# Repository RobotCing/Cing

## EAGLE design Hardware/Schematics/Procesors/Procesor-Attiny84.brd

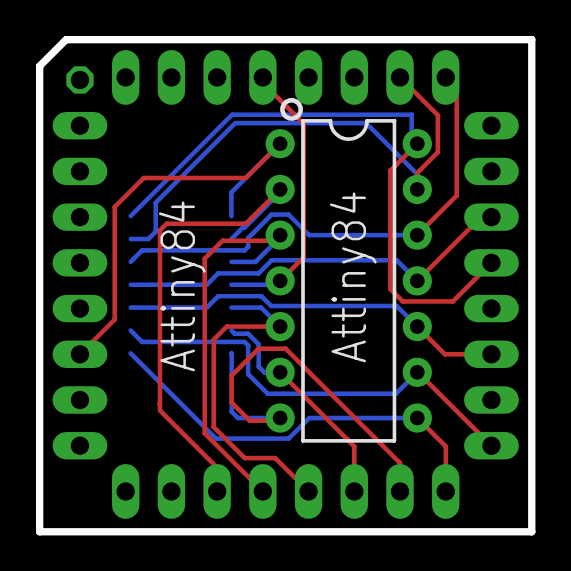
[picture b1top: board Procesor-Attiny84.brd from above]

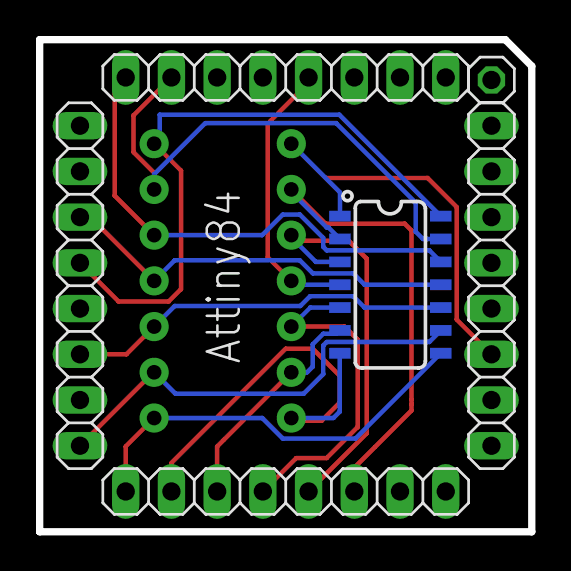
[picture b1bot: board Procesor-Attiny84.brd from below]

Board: 2 copper layers, 27.3 x 27.3 mm, 7 parts (6 on the bottom side), 14 nets.

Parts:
E$1: DIP14
E$2: 1X01
E$3: SO14
E$9, E$10, E$11, E$12: 1X08

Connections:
S$2: E$1.4, E$3.4, E$10.5
S$3: E$1.14, E$3.14, E$11.4
S$4: E$1.1, E$3.1, E$9.3
S$5: E$1.9, E$3.9, E$11.8
S$6: E$1.12, E$3.12, E$10.1
S$7: E$1.13, E$3.13, E$10.2
S$8: E$1.7, E$3.7, E$12.7
S$10: E$1.8, E$3.8, E$12.8
S$11: E$1.10, E$3.10, E$11.6
S$12: E$1.11, E$3.11, E$11.3
S$13: E$1.2, E$3.2, E$12.3
S$14: E$1.3, E$3.3, E$12.4
S$15: E$1.5, E$3.5, E$12.5
S$18: E$1.6, E$3.6, E$12.6

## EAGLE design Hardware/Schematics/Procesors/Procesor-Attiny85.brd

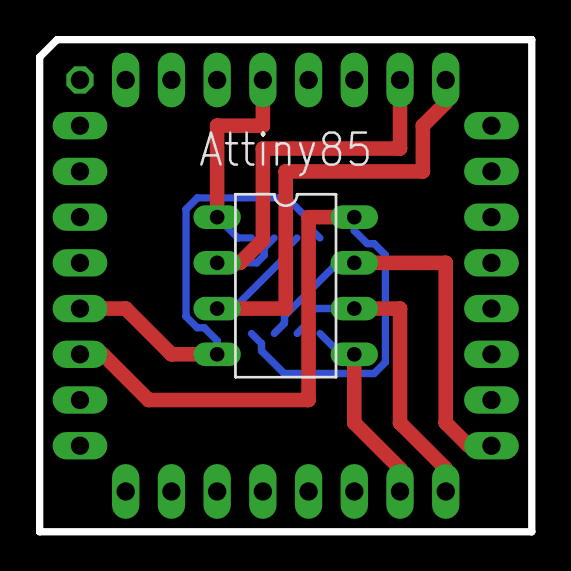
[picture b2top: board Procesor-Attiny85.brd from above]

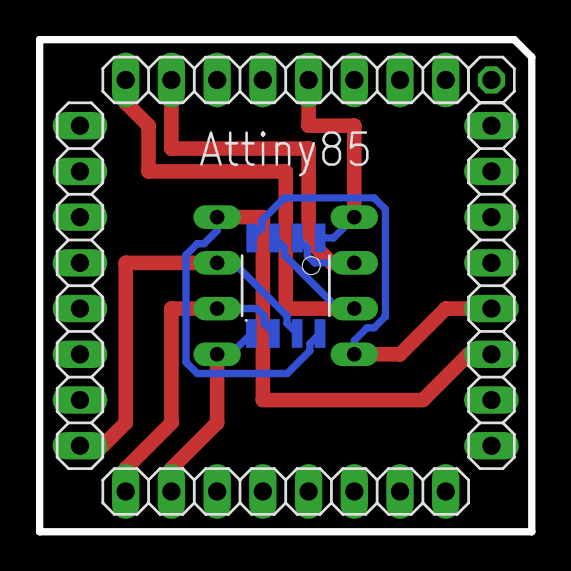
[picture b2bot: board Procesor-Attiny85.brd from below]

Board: 2 copper layers, 27.3 x 27.3 mm, 7 parts (6 on the bottom side), 8 nets.

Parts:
ATTINY85: DIL08
E$1: 1X01
E$2: 8S1
E$9, E$10, E$11, E$12: 1X08

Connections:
S$2: ATTINY85.1, E$2.1, E$10.5
S$3: ATTINY85.4, E$2.4, E$9.4
S$4: ATTINY85.8, E$2.8, E$9.3
S$5: ATTINY85.7, E$2.7, E$11.8
S$6: ATTINY85.3, E$2.3, E$10.1
S$7: ATTINY85.2, E$2.2, E$10.2
S$8: ATTINY85.5, E$2.5, E$12.7
S$10: ATTINY85.6, E$2.6, E$12.8

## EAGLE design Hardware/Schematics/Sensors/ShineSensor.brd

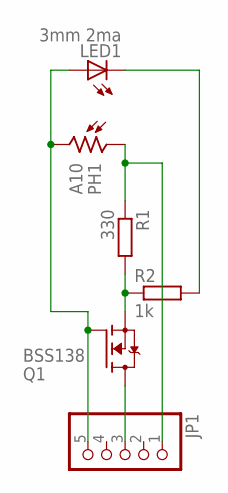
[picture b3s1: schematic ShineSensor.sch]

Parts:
JP1: PINHD-1X5; 1X05
LED1: 3mm 2ma; LED3MM
PH1: A10; T0-46-A10XX
Q1: BSS138; SOT23
R1: 330; R1206
R2: 1k; R1206

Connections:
unnamed: JP1.5, LED1.A, PH1.2, Q1.1 (G)
unnamed: LED1.K (C), R2.2
unnamed: JP1.3, Q1.3 (D)
unnamed: JP1.1, PH1.1, R1.1
unnamed: Q1.2 (S), R1.2, R2.1

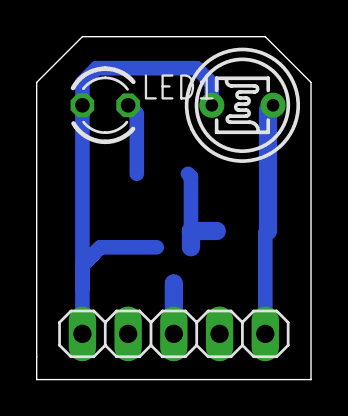
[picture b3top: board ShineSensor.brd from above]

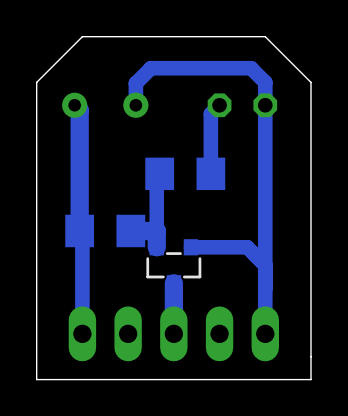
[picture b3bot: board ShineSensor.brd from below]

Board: 2 copper layers, 15.2 x 19.1 mm, 6 parts (3 on the bottom side), 5 nets.

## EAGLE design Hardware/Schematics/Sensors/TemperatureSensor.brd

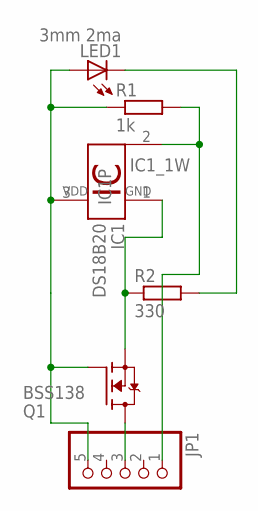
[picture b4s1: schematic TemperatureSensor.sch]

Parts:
IC1: DS18B20; TO92-
JP1: PINHD-1X5; 1X05
LED1: 3mm 2ma; LED3MM
Q1: BSS138; SOT23
R1: 1k; R1206
R2: 330; R1206

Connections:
unnamed: IC1.3 (VDD), JP1.5, LED1.A, Q1.1 (G), R1.1
unnamed: LED1.K (C), R2.2
unnamed: JP1.3, Q1.3 (D)
unnamed: IC1.1 (GND), Q1.2 (S), R2.1
unnamed: IC1.2 (1W), JP1.1, R1.2

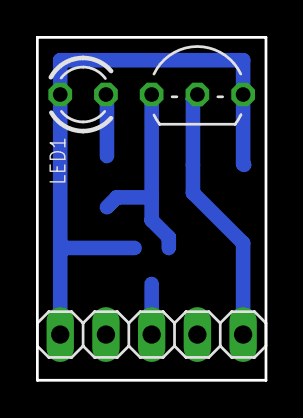
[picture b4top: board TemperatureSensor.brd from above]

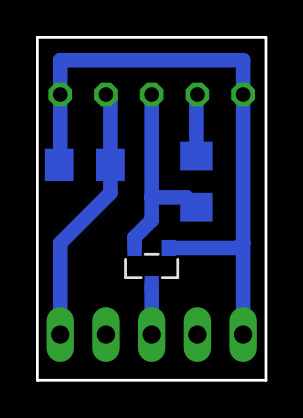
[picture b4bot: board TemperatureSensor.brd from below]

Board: 2 copper layers, 12.7 x 19.1 mm, 6 parts (3 on the bottom side), 5 nets.

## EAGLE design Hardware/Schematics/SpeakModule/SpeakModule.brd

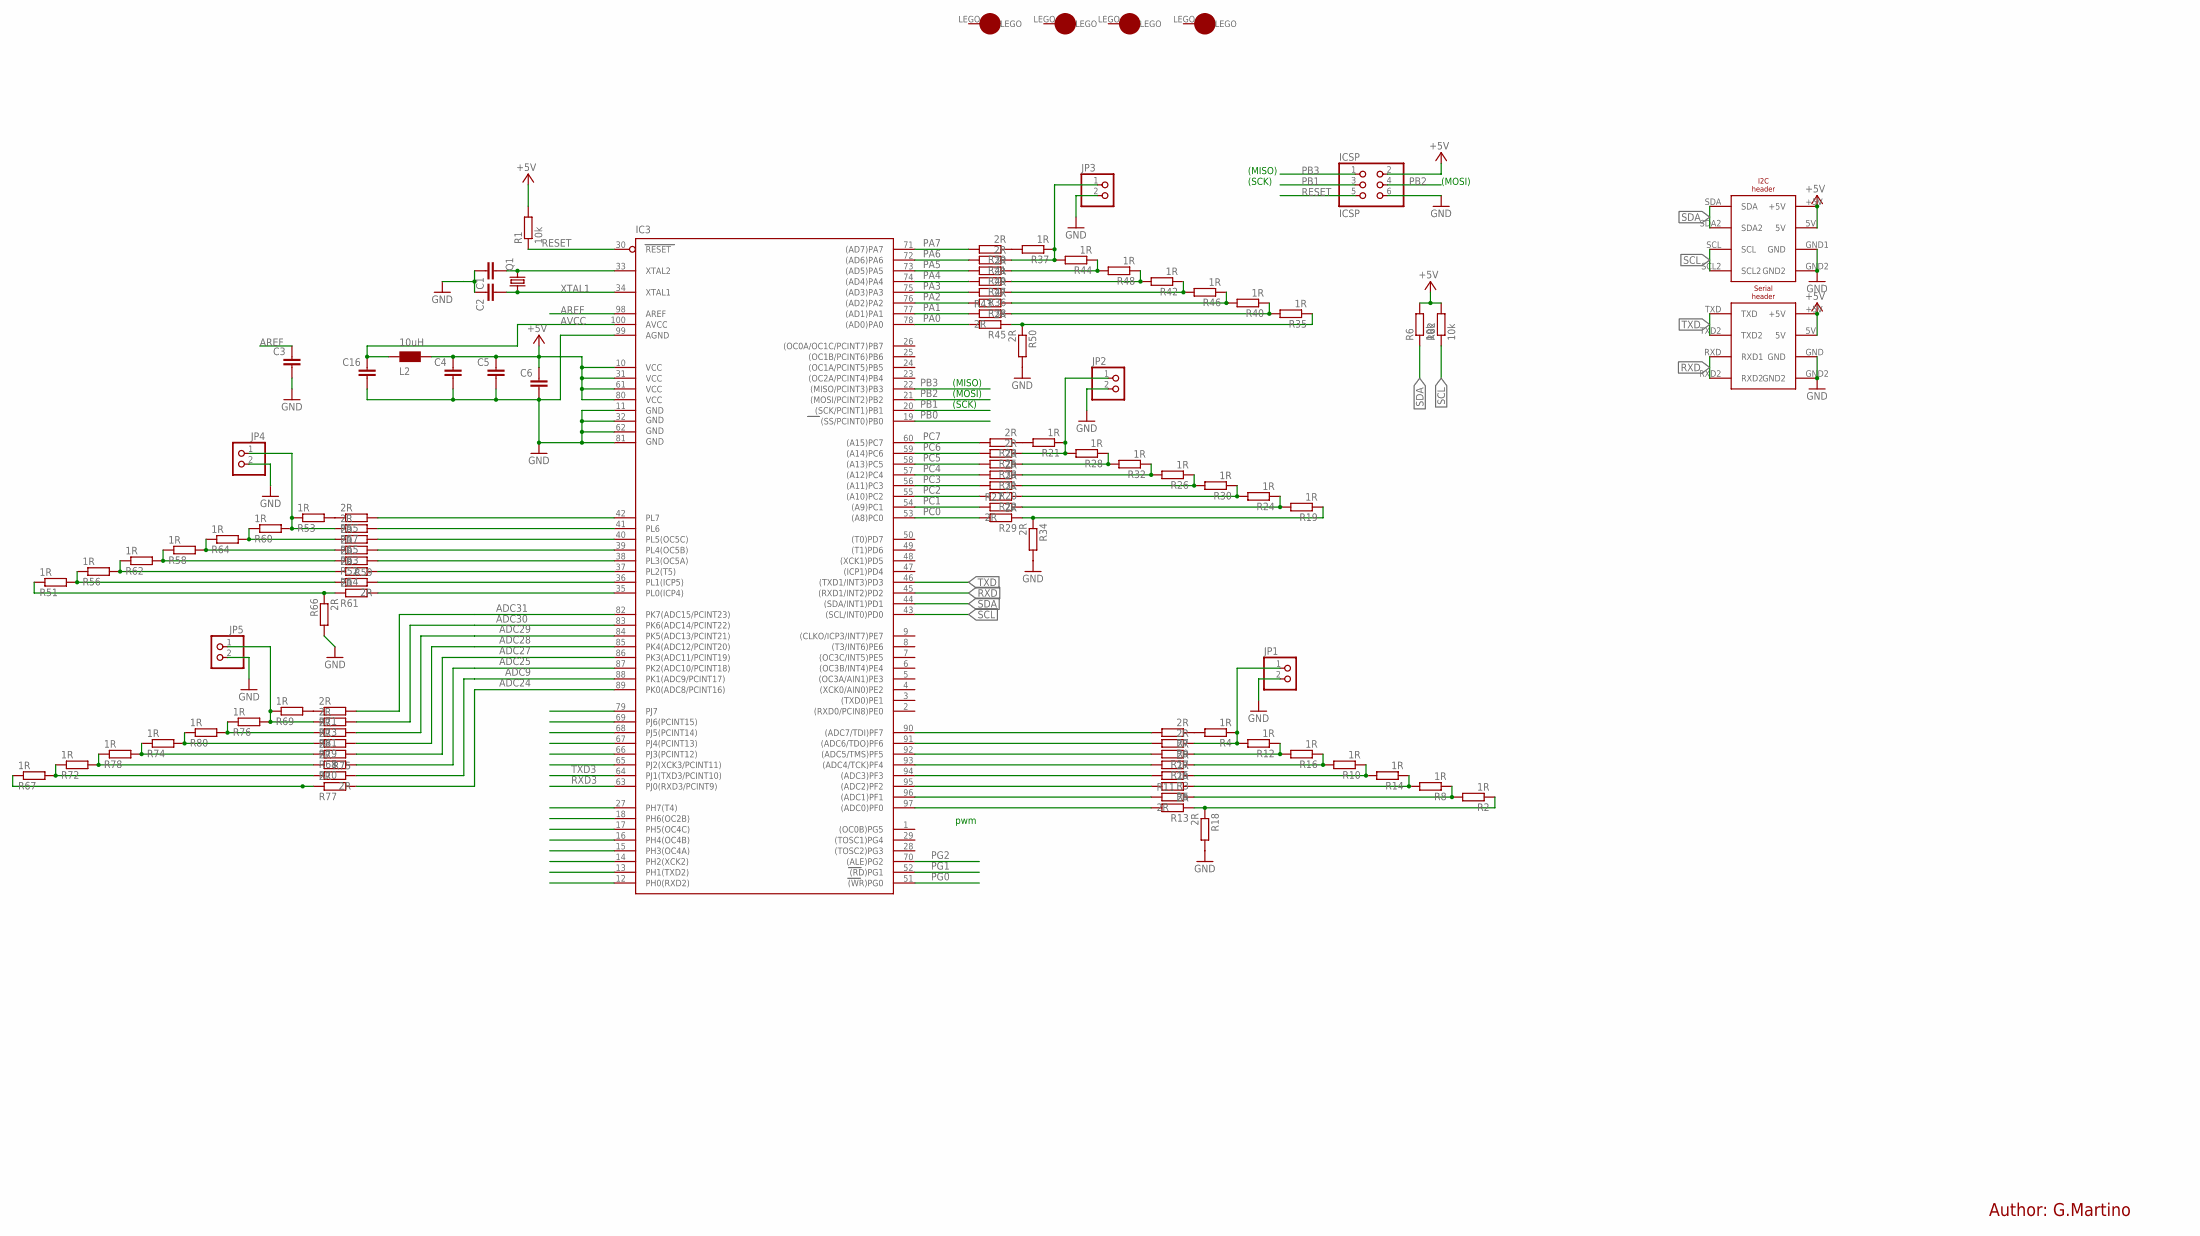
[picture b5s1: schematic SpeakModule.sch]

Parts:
C1, C2: 22pf; C1206
C3, C4, C5, C6, C16: 100nF; C1206
IC3: ATMEGA2560-15AU; TQFP100
ICSP: ICSP; 2X03
JP1, JP2, JP3, JP4, JP5: PINHD-1X2; 1X02
L2: 10uH; 0805
Q1: CRYSTALHC49S; HC49/S
R1, R6, R82: 10k; M1206
R2, R4, R8, R10, R12, R14, R16, R19, R21, R24, R26, R28, R30, R32, R35, R37, R40, R42, R44, R46, R48, R51, R53, R56, R58, R60, R62, R64, R67, R69, R72, R74, R76, R78, R80: 1R; M1206
R3, R5, R7, R9, R11, R13, R15, R17, R18, R20, R22, R23, R25, R27, R29, R31, R33, R34, R36, R38, R39, R41, R43, R45, R47, R49, R50, R52, R54, R55, R57, R59, R61, R63, R65, R66, R68, R70, R71, R73, R75, R77, R79, R81: 2R; M1206
U$1, U$2, U$3, U$4: LEGO-1X1
U$5: I2C_HEADER; I2_HEADER
U$6: SERIAL_HEADER

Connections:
+5V: C4.1, C5.1, C6.1, IC3.10 (VCC), IC3.31 (VCC1), IC3.61 (VCC2), IC3.80 (VCC3), ICSP.2, L2.2, R1.2, R6.2, R82.2, U$5.5V, U$5.+5V, U$6.5V, U$6.+5V
ADC0: IC3.97 ((ADC0)PF0), R13.2
ADC1: IC3.96 ((ADC1)PF1), R11.1
ADC2: IC3.95 ((ADC2)PF2), R5.2
ADC3: IC3.94 ((ADC3)PF3), R3.2
ADC4: IC3.93 ((ADC4/TCK)PF4), R15.2
ADC5: IC3.92 ((ADC5/TMS)PF5), R17.2
ADC6: IC3.91 ((ADC6/TDO)PF6), R9.2
ADC7: IC3.90 ((ADC7/TDI)PF7), R7.2
ADC9: IC3.88 (PK1(ADC9/PCINT17)), R75.1
ADC16: IC3.35 (PL0(ICP4)), R61.2
ADC17: IC3.37 (PL2(T5)), R54.2
ADC18: IC3.36 (PL1(ICP5)), R59.1
ADC19: IC3.38 (PL3(OC5A)), R52.2
ADC20: IC3.39 (PL4(OC5B)), R63.2
ADC21: IC3.40 (PL5(OC5C)), R65.2
ADC22: IC3.41 (PL6), R57.2
ADC23: IC3.42 (PL7), R55.2
ADC24: IC3.89 (PK0(ADC8/PCINT16)), R77.2
ADC25: IC3.87 (PK2(ADC10/PCINT18)), R70.2
ADC27: IC3.86 (PK3(ADC11/PCINT19)), R68.2
ADC28: IC3.85 (PK4(ADC12/PCINT20)), R79.2
ADC29: IC3.84 (PK5(ADC13/PCINT21)), R81.2
ADC30: IC3.83 (PK6(ADC14/PCINT22)), R73.2
ADC31: IC3.82 (PK7(ADC15/PCINT23)), R71.2
AREF: C3.1, IC3.98 (AREF)
AVCC: C16.1, IC3.100 (AVCC), L2.1
GND: C1.1, C2.1, C3.2, C4.2, C5.2, C6.2, C16.2, IC3.11 (GND), IC3.32 (GND1), IC3.62 (GND2), IC3.81 (GND3), IC3.99 (AGND), ICSP.6, JP1.2, JP2.2, JP3.2, JP4.2, JP5.2, R18.2, R34.2, R50.2, R66.2, U$5.GND1 (GND), U$5.GND2, U$6.GND, U$6.GND2
unnamed: C1.2, IC3.33 (XTAL2), Q1.2
unnamed: R4.2, R7.1
unnamed: JP1.1, R4.1, R9.1, R12.2
unnamed: R12.1, R16.2, R17.1
unnamed: R10.2, R15.1, R16.1
unnamed: R3.1, R10.1, R14.2
unnamed: R5.1, R8.2, R14.1
unnamed: R2.2, R8.1, R11.2
unnamed: R2.1, R13.1, R18.1
unnamed: R21.2, R23.1
unnamed: JP2.1, R21.1, R25.1, R28.2
unnamed: R28.1, R32.2, R33.1
unnamed: R26.2, R31.1, R32.1
unnamed: R20.1, R26.1, R30.2
unnamed: R22.1, R24.2, R30.1
unnamed: R19.2, R24.1, R27.2
unnamed: R19.1, R29.1, R34.1
unnamed: R37.2, R39.1
unnamed: JP3.1, R37.1, R41.1, R44.2
unnamed: R44.1, R48.2, R49.1
unnamed: R42.2, R47.1, R48.1
unnamed: R36.1, R42.1, R46.2
unnamed: R38.1, R40.2, R46.1
unnamed: R35.2, R40.1, R43.2
unnamed: R35.1, R45.1, R50.1
unnamed: R53.2, R55.1
unnamed: JP4.1, R53.1, R57.1, R60.2
unnamed: R60.1, R64.2, R65.1
unnamed: R58.2, R63.1, R64.1
unnamed: R52.1, R58.1, R62.2
unnamed: R54.1, R56.2, R62.1
unnamed: R51.2, R56.1, R59.2
unnamed: R51.1, R61.1, R66.1
unnamed: R69.2, R71.1
unnamed: JP5.1, R69.1, R73.1, R76.2
unnamed: R76.1, R80.2, R81.1
unnamed: R74.2, R79.1, R80.1
unnamed: R68.1, R74.1, R78.2
unnamed: R70.1, R72.2, R78.1
unnamed: R67.2, R72.1, R75.2
unnamed: R67.1, R77.1
PA0: IC3.78 ((AD0)PA0), R45.2
PA1: IC3.77 ((AD1)PA1), R43.1
PA2: IC3.76 ((AD2)PA2), R38.2
PA3: IC3.75 ((AD3)PA3), R36.2
PA4: IC3.74 ((AD4)PA4), R47.2
PA5: IC3.73 ((AD5)PA5), R49.2
PA6: IC3.72 ((AD6)PA6), R41.2
PA7: IC3.71 ((AD7)PA7), R39.2
PB0: IC3.19 ((SS/PCINT0)PB0)
PB1: IC3.20 ((SCK/PCINT1)PB1), ICSP.3
PB2: IC3.21 ((MOSI/PCINT2)PB2), ICSP.4
PB3: IC3.22 ((MISO/PCINT3)PB3), ICSP.1
PC0: IC3.53 ((A8)PC0), R29.2
PC1: IC3.54 ((A9)PC1), R27.1
PC2: IC3.55 ((A10)PC2), R22.2
PC3: IC3.56 ((A11)PC3), R20.2
PC4: IC3.57 ((A12)PC4), R31.2
PC5: IC3.58 ((A13)PC5), R33.2
PC6: IC3.59 ((A14)PC6), R25.2
PC7: IC3.60 ((A15)PC7), R23.2
PG0: IC3.51 ((WR)PG0)
PG1: IC3.52 ((RD)PG1)
PG2: IC3.70 ((ALE)PG2)
RESET: IC3.30 (RESET), ICSP.5, R1.1
RXD: IC3.45 ((RXD1/INT2)PD2), U$6.RXD (RXD1), U$6.RXD2
RXD3: IC3.63 (PJ0(RXD3/PCINT9))
SCL: IC3.43 ((SCL/INT0)PD0), R82.1, U$5.SCL, U$5.SCL2
SDA: IC3.44 ((SDA/INT1)PD1), R6.1, U$5.SDA, U$5.SDA2
TXD: IC3.46 ((TXD1/INT3)PD3), U$6.TXD, U$6.TXD2
TXD3: IC3.64 (PJ1(TXD3/PCINT10))
XTAL1: C2.2, IC3.34 (XTAL1), Q1.1

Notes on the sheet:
(SCK)
(MISO)
(MOSI)
pwm
Author: G.Martino

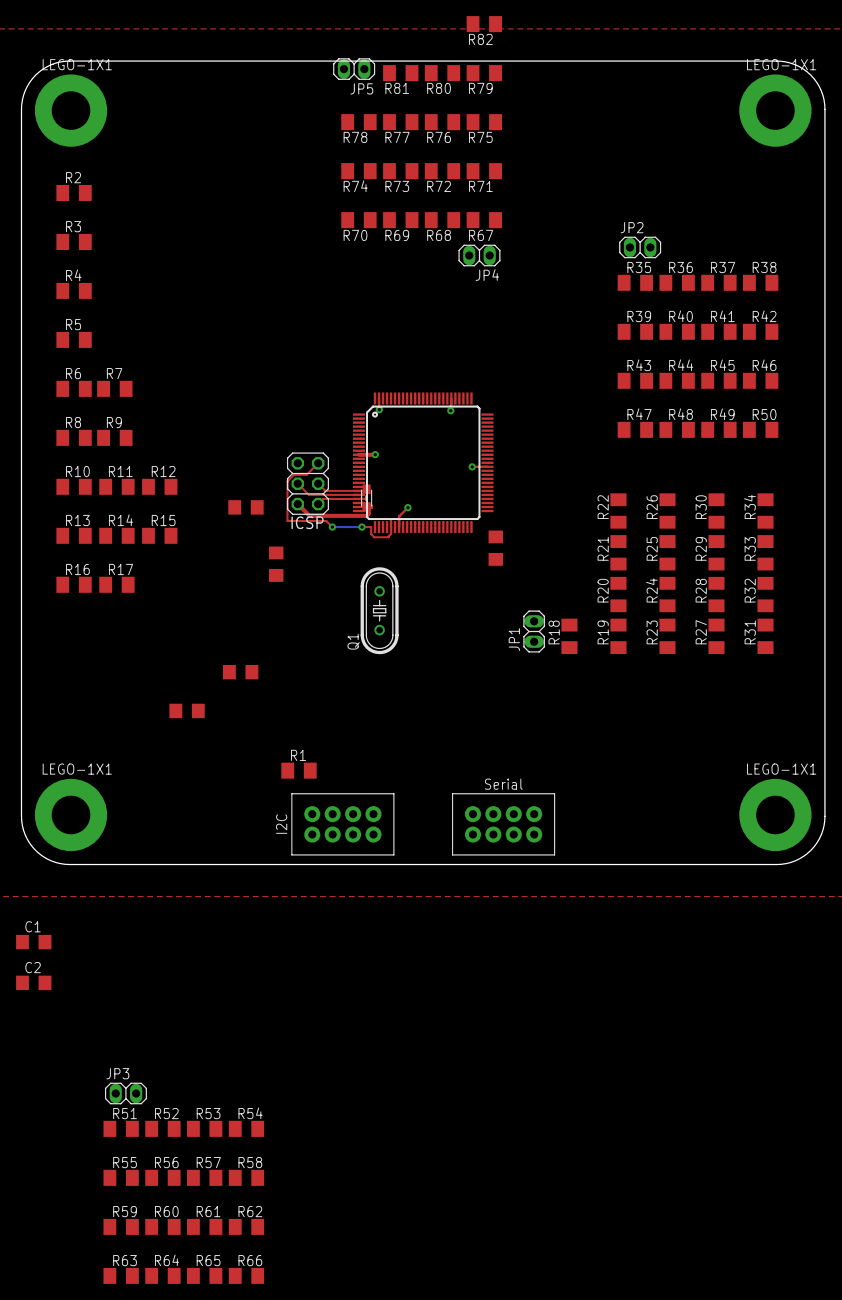
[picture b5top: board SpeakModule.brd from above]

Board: 2 copper layers, 100.0 x 100.0 mm, 104 parts (0 on the bottom side), 94 nets.

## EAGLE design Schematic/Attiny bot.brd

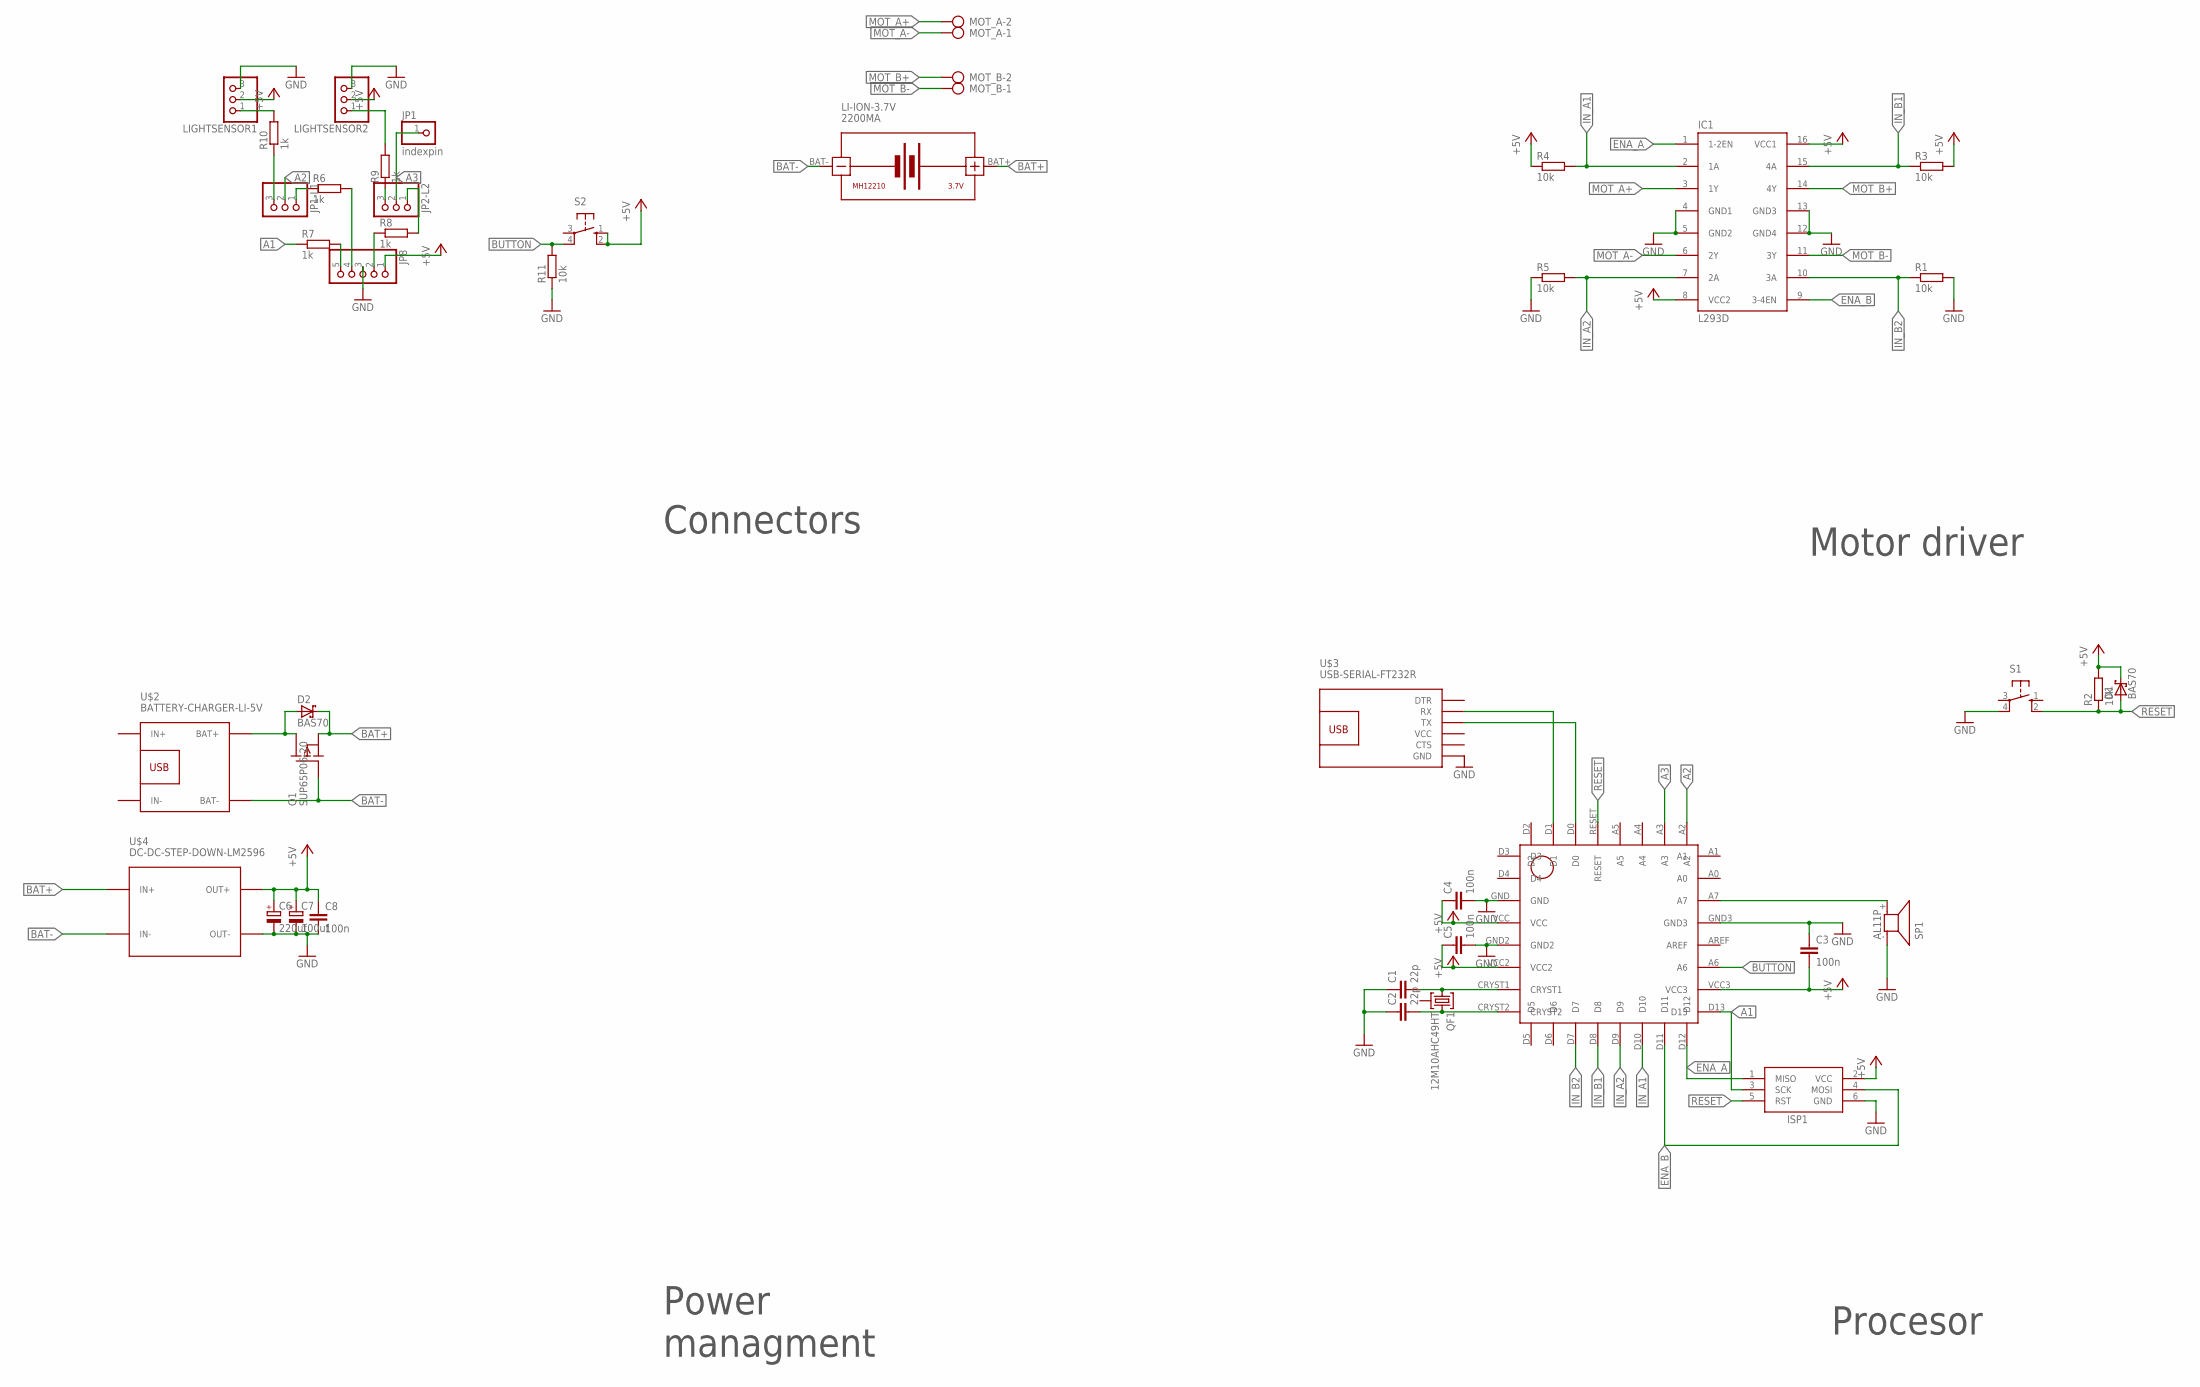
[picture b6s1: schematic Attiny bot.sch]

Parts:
C1, C2: 22p; C1206
C3, C4, C5, C8: 100n; C1206
C6: 220uf; E3,5-8
C7: 100uf; E3,5-8
D1, D2: BAS70; SOT23
IC1: L293D; DIL16
ISP1: AVRISP-6; AVRISP
JP1: indexpin; 1X01
JP1-L1, JP2-L2: PINHD-1X3; 1X03
JP8: PINHD-1X5; 1X05
LI-ION-3.7V: 2200MA; BATTERY-LI-MH12210
LIGHTSENSOR1, LIGHTSENSOR2: PINHD-1X3; 1X03
MOT_A: AK500/2
MOT_B: AK500/2
Q1: SUP65P06-20; TO220
QF1: 12M10AHC49HT; HC49U
R1, R2, R3, R4, R5, R11: 10k; R1206
R6, R7, R8, R9, R10: 1k; R1206
S1, S2: 10-XX; B3F-10XX
SP1: AL11P
U$1: PROCESSOR; PROCESOR
U$2: BATTERY-CHARGER-LI-5V
U$3: USB-SERIAL-FT232R
U$4: DC-DC-STEP-DOWN-LM2596

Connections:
+5V: C3.2, C4.1, C5.1, C6.+, C7.+, C8.1, D1.3 (C), IC1.8 (VCC2), IC1.16 (VCC1), ISP1.2 (VCC), JP8.1, LIGHTSENSOR1.2, LIGHTSENSOR2.2, R2.2, R3.2, R4.1, S2.1 (S), S2.2 (S1), U$1.VCC, U$1.VCC2, U$1.VCC3, U$4.OUT+
A1: ISP1.3 (SCK), R7.1, U$1.D13
A2: JP1-L1.2, U$1.A2
A3: JP1.1, JP2-L2.2, U$1.A3
BAT+: D2.3 (C), LI-ION-3.7V.BAT+, Q1.3 (S), U$4.IN+
BAT-: LI-ION-3.7V.BAT-, Q1.1 (G), U$2.BAT-, U$4.IN-
BUTTON: R11.2, S2.4 (P1), U$1.A6
ENA_A: IC1.1 (1-2EN), ISP1.1 (MISO), U$1.D12
ENA_B: IC1.9 (3-4EN), ISP1.4 (MOSI), U$1.D11
GND: C1.1, C2.1, C3.1, C4.2, C5.2, C6.-, C7.-, C8.2, IC1.4 (GND1), IC1.5 (GND2), IC1.12 (GND4), IC1.13 (GND3), ISP1.6 (GND), JP8.3, LIGHTSENSOR1.3, LIGHTSENSOR2.3, R1.2, R5.1, R11.1, S1.4 (P1), SP1.- (1), U$1.GND, U$1.GND2, U$1.GND3, U$3.6 (GND), U$4.OUT-
IN_A1: IC1.2 (1A), R4.2, U$1.D10
IN_A2: IC1.7 (2A), R5.2, U$1.D9
IN_B1: IC1.15 (4A), R3.1, U$1.D8
IN_B2: IC1.10 (3A), R1.1, U$1.D7
MOT_A+: IC1.3 (1Y), MOT_A.2
MOT_A-: IC1.6 (2Y), MOT_A.1
MOT_B+: IC1.14 (4Y), MOT_B.2
MOT_B-: IC1.11 (3Y), MOT_B.1
unnamed: JP1-L1.1, R6.1
unnamed: JP8.2, R8.1
unnamed: C2.2, QF1.3, U$1.CRYST2
unnamed: C1.2, QF1.1, U$1.CRYST1
unnamed: LIGHTSENSOR2.1, R9.2
unnamed: U$1.D1, U$3.2 (RX)
unnamed: LIGHTSENSOR1.1, R10.2
unnamed: JP2-L2.3, R9.1
unnamed: JP8.5, R7.2
unnamed: JP8.4, R6.2
unnamed: JP2-L2.1, R8.2
unnamed: JP1-L1.3, R10.1
unnamed: D2.1 (A), Q1.2 (D), U$2.BAT+
unnamed: SP1.+ (2), U$1.A7
unnamed: U$1.D0, U$3.3 (TX)
RESET: D1.1 (A), ISP1.5 (RST), R2.1, S1.2 (S1), U$1.RESET
VCC: U$3.4 (VCC)

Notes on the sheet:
Connectors
Motor driver
Procesor
Power managment

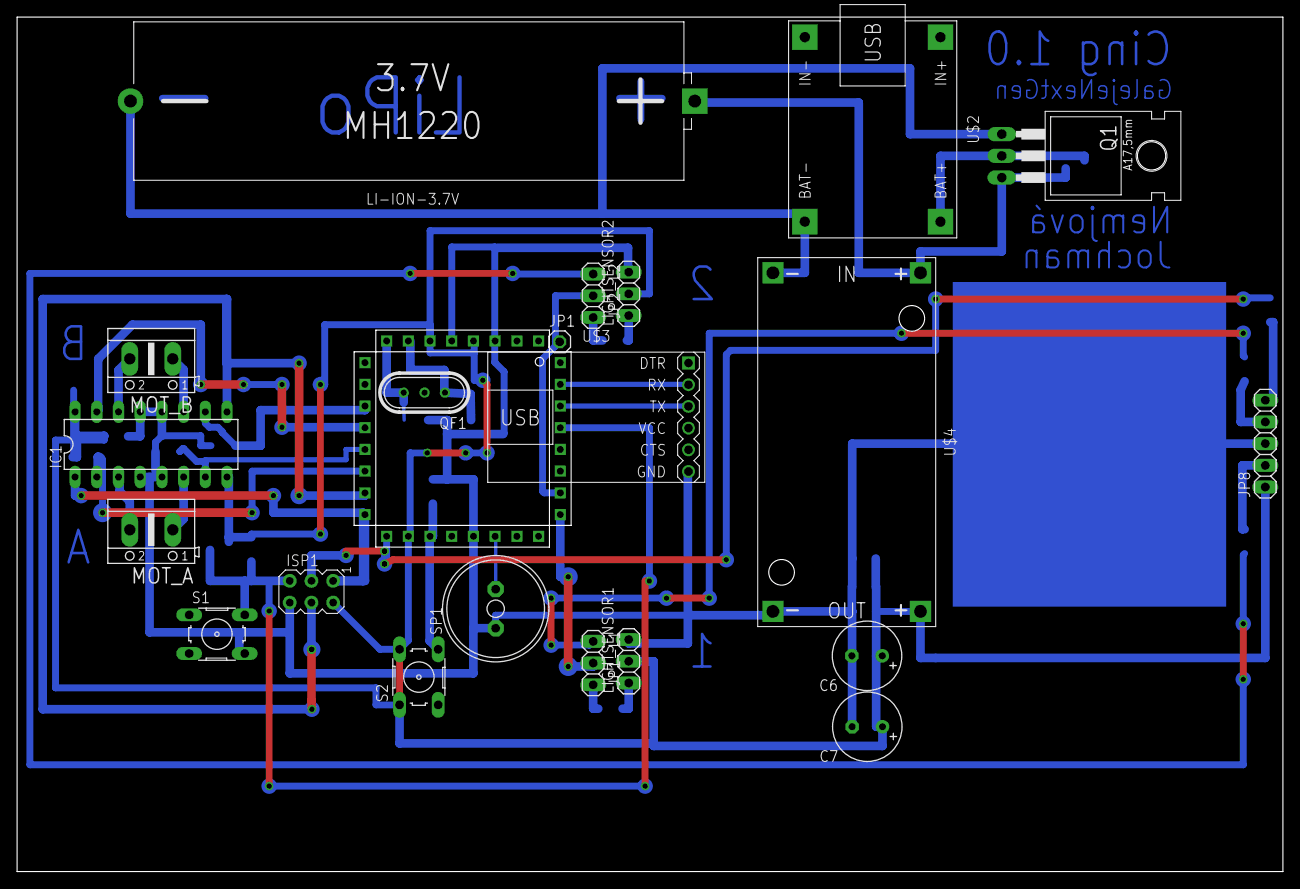
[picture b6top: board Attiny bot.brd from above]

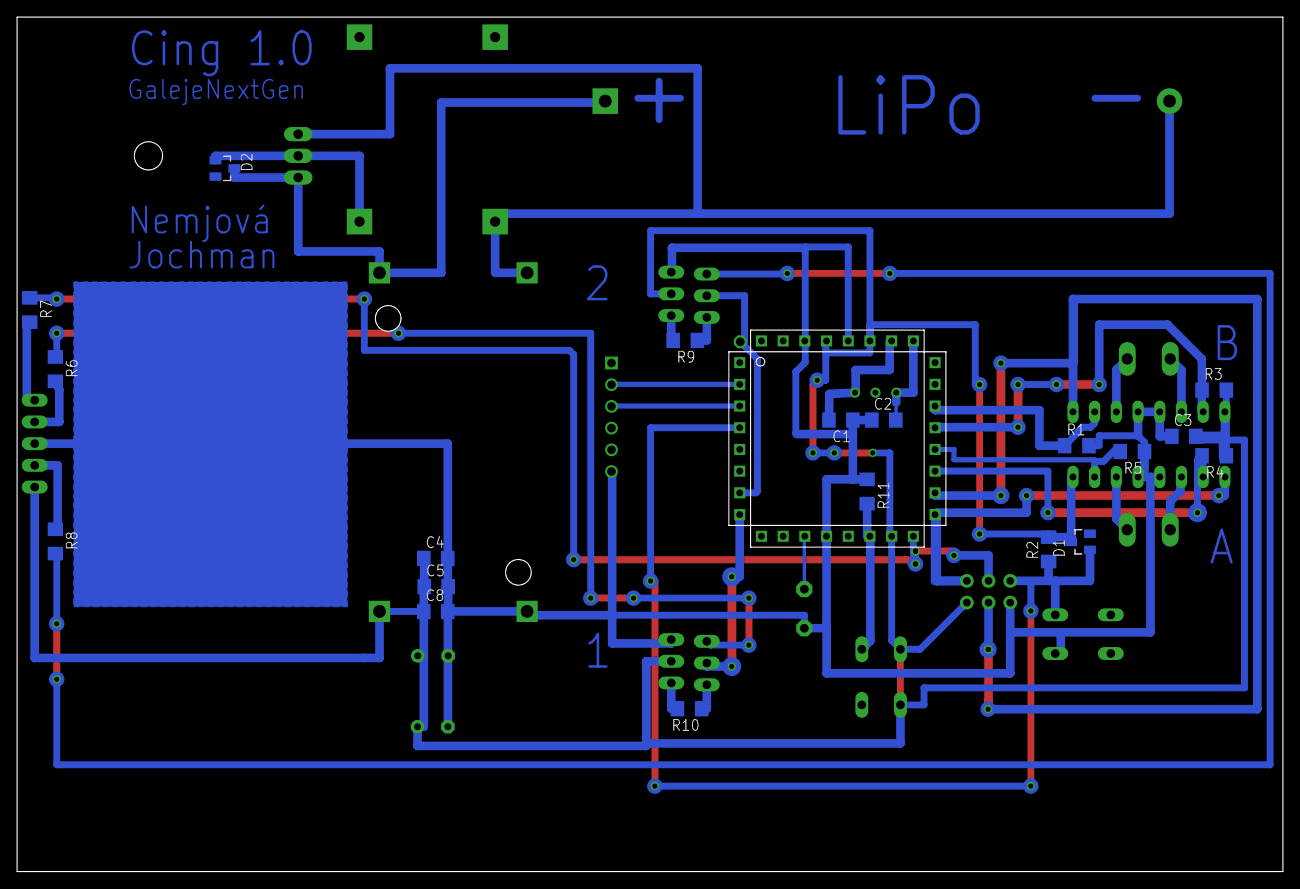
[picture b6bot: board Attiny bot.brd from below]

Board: 2 copper layers, 148.1 x 100.0 mm, 41 parts (19 on the bottom side), 34 nets.

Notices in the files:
parts and their libraries:
SparkFun-IC-Microcontroller: Licensing: Creative Commons ShareAlike 4.0 International - https://creativecommons.org/licenses/by-sa/4.0
diy-modules: Released under the Creative Commons Attribution 4.0 International License: http://creativecommons.org/licenses/by/4.0
